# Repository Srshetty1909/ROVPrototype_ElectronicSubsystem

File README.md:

# ROVPrototype_ElectronicSubsystem
The Electronics Architecture for an ROV Prototype meant to test various subsystems for a future AUV before final integration.

Control Architecture:

Power Distribution:

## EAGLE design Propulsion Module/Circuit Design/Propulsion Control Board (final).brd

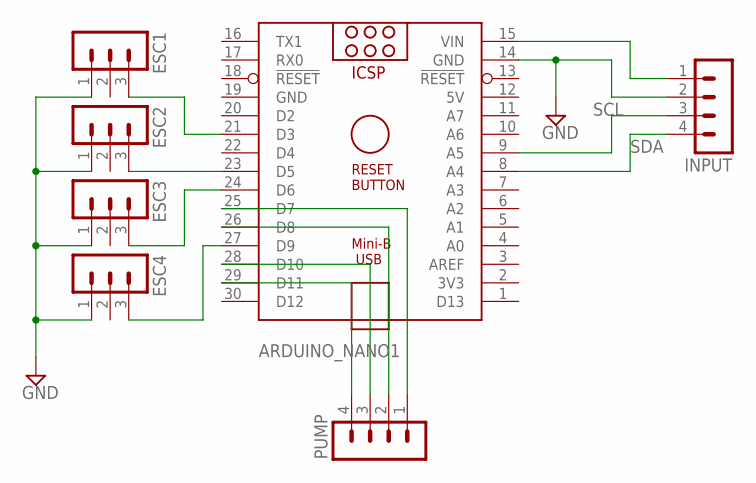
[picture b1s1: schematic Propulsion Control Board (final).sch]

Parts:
ARDUINO_NANO1: ARDUINO_NANO
ESC1, ESC2, ESC3, ESC4: MA03-1
INPUT: MA04-1
PUMP: MA04-1

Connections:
5V: ARDUINO_NANO1.12 (5V)
GND: ARDUINO_NANO1.14 (GND), ARDUINO_NANO1.19 (GND), ESC1.1, ESC2.1, ESC3.1, ESC4.1, INPUT.2
unnamed: ARDUINO_NANO1.21 (D3), ESC1.3
unnamed: ARDUINO_NANO1.23 (D5), ESC2.3
unnamed: ARDUINO_NANO1.24 (D6), ESC3.3
unnamed: ARDUINO_NANO1.27 (D9), ESC4.3
unnamed: ARDUINO_NANO1.25 (D7), PUMP.1
unnamed: ARDUINO_NANO1.26 (D8), PUMP.2
unnamed: ARDUINO_NANO1.28 (D10), PUMP.3
unnamed: ARDUINO_NANO1.29 (D11), PUMP.4
unnamed: ARDUINO_NANO1.15 (VIN), INPUT.1
SCL: ARDUINO_NANO1.9 (A5), INPUT.3
SDA: ARDUINO_NANO1.8 (A4), INPUT.4

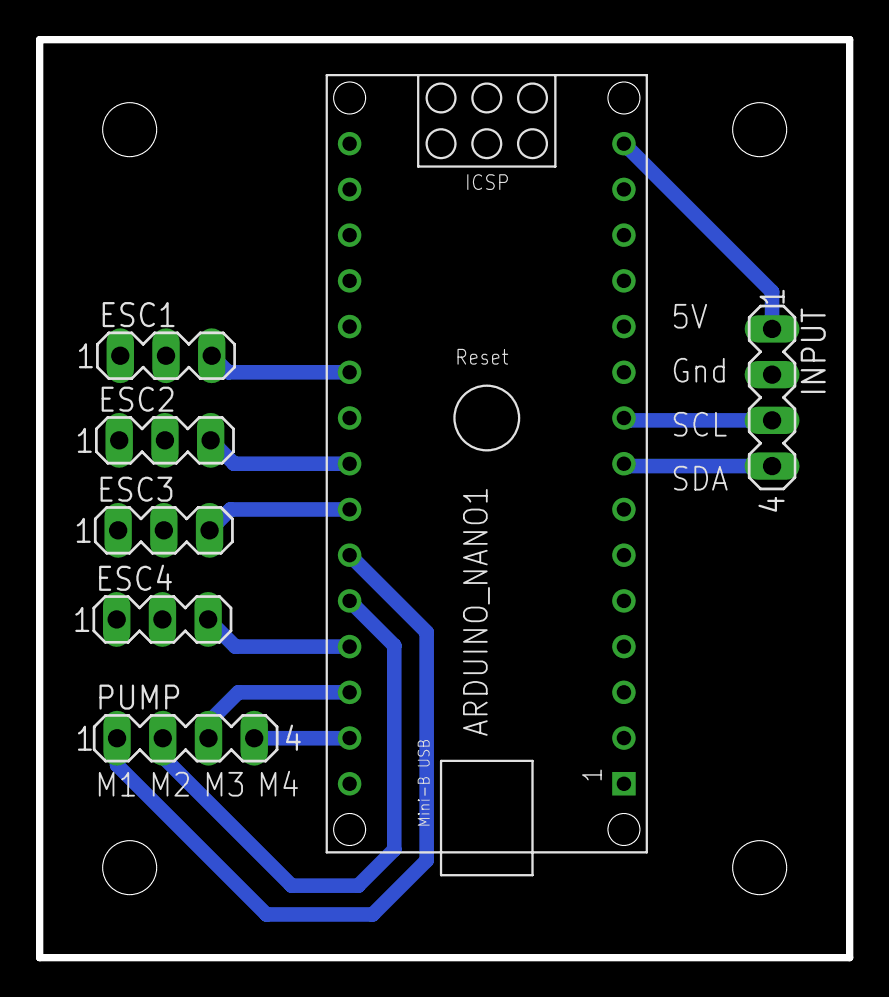
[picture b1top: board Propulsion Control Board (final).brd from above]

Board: 2 copper layers, 45.0 x 51.0 mm, 7 parts (0 on the bottom side), 12 nets.

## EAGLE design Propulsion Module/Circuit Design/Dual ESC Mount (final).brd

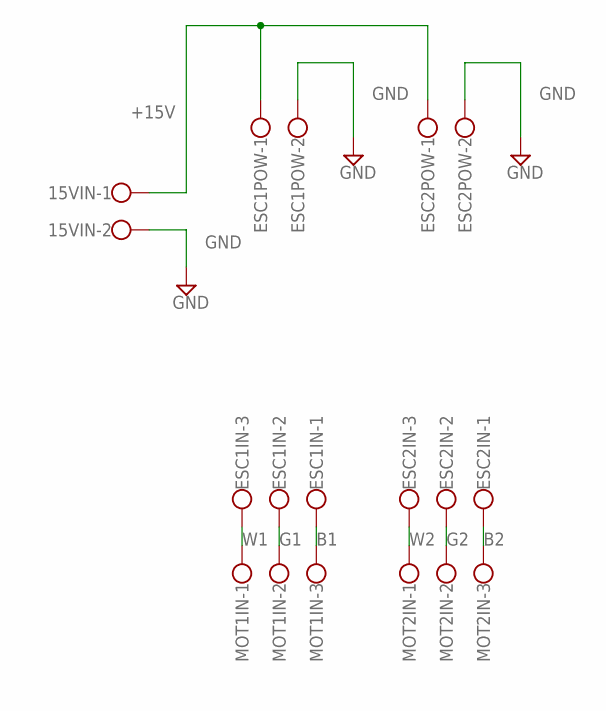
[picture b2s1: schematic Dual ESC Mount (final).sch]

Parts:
15VIN: W237-102
ESC1IN, ESC2IN: W237-103
ESC1POW, ESC2POW: W237-102
MOT1IN, MOT2IN: W237-103

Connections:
+15V: 15VIN.1, ESC1POW.1, ESC2POW.1
B1: ESC1IN.1, MOT1IN.3
B2: ESC2IN.1, MOT2IN.3
G1: ESC1IN.2, MOT1IN.2
G2: ESC2IN.2, MOT2IN.2
GND: 15VIN.2, ESC1POW.2, ESC2POW.2
W1: ESC1IN.3, MOT1IN.1
W2: ESC2IN.3, MOT2IN.1

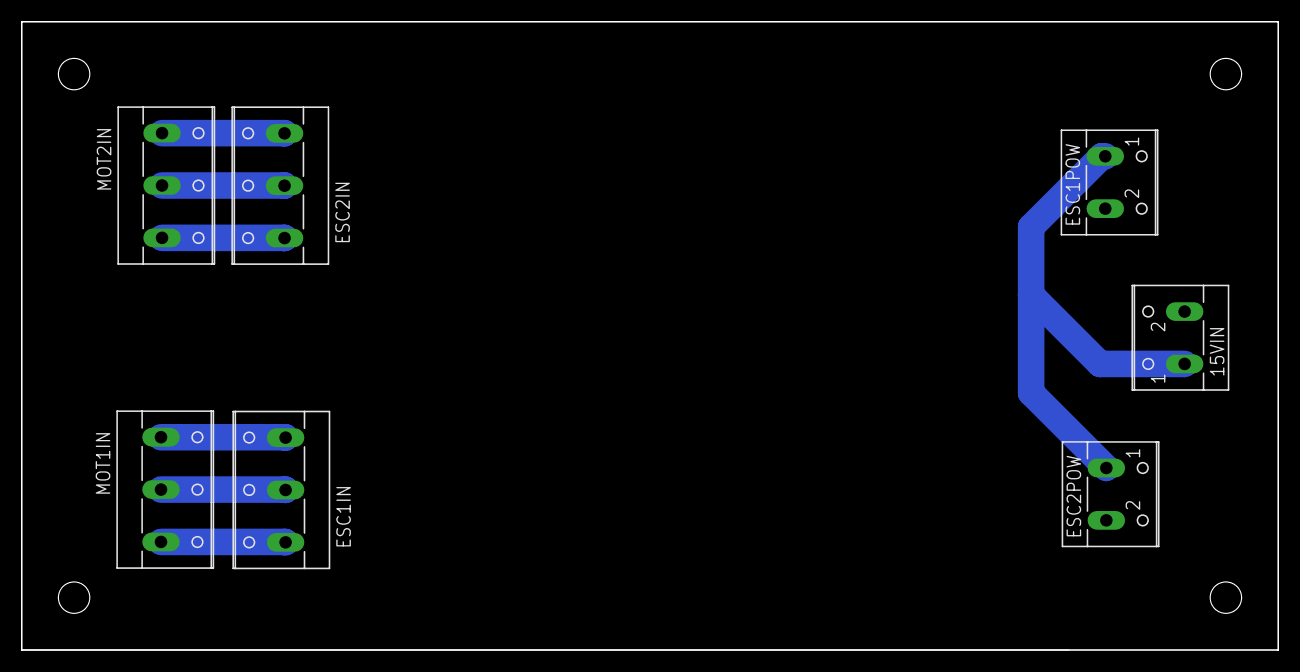
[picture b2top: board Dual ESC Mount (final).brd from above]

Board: 2 copper layers, 120.0 x 60.0 mm, 7 parts (0 on the bottom side), 8 nets.

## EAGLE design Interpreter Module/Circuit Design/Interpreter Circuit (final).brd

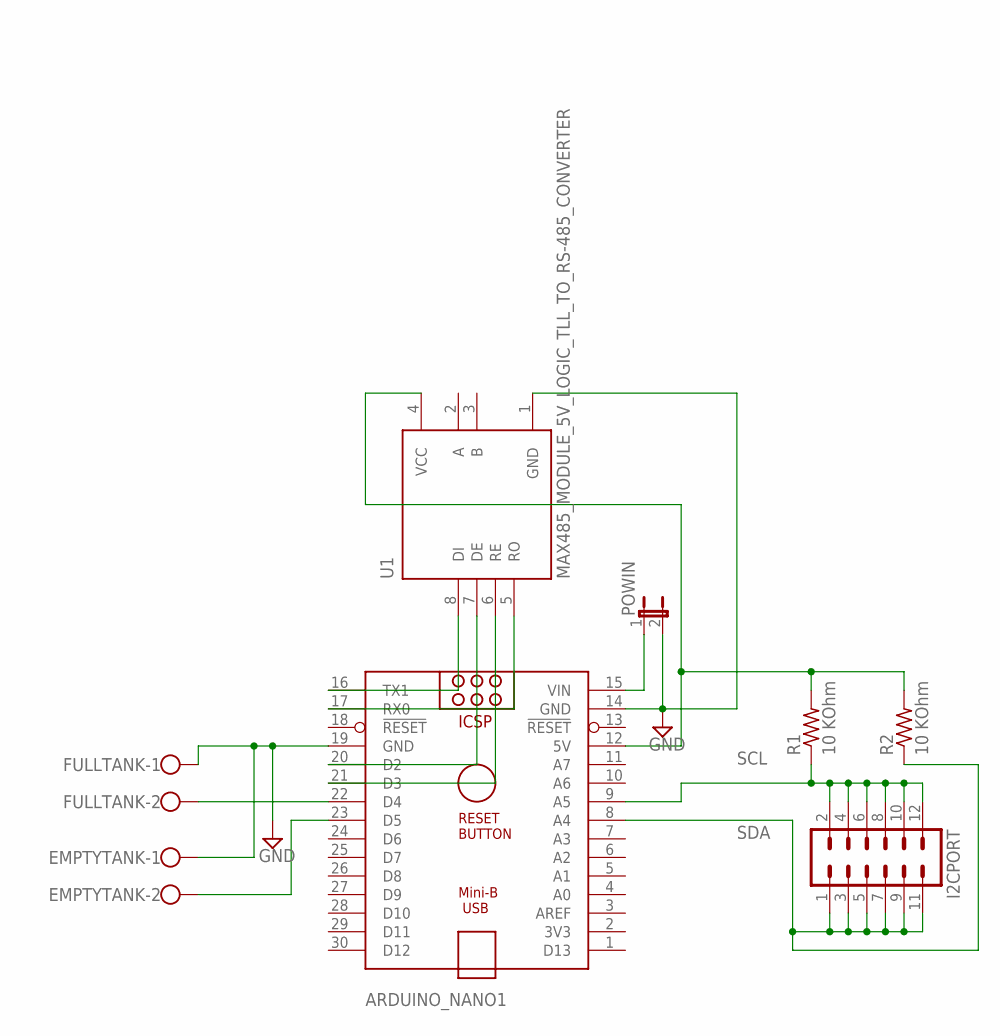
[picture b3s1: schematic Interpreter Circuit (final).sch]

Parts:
ARDUINO_NANO1: ARDUINO_NANO
EMPTYTANK: W237-102
FULLTANK: W237-102
I2CPORT: MA06-2
POWIN: JP1E; JP1
R1, R2: 10 KOhm; 0204/7
U1: MAX485_MODULE_5V_LOGIC_TLL_TO_RS-485_CONVERTER; MODULE_MAX485_MODULE_5V_LOGIC_TLL_TO_RS-485_CONVERTER

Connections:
GND: ARDUINO_NANO1.14 (GND), ARDUINO_NANO1.19 (GND), EMPTYTANK.1, FULLTANK.1, POWIN.2, U1.1 (GND)
unnamed: ARDUINO_NANO1.17 (RX0), U1.5 (RO)
unnamed: ARDUINO_NANO1.16 (TX1), U1.8 (DI)
unnamed: ARDUINO_NANO1.20 (D2), U1.7 (DE)
unnamed: ARDUINO_NANO1.21 (D3), U1.6 (RE)
unnamed: ARDUINO_NANO1.22 (D4), FULLTANK.2
unnamed: ARDUINO_NANO1.12 (5V), R1.2, R2.2, U1.4 (VCC)
unnamed: ARDUINO_NANO1.23 (D5), EMPTYTANK.2
unnamed: ARDUINO_NANO1.15 (VIN), POWIN.1
SCL: ARDUINO_NANO1.9 (A5), I2CPORT.2, I2CPORT.4, I2CPORT.6, I2CPORT.8, I2CPORT.10, I2CPORT.12, R1.1
SDA: ARDUINO_NANO1.8 (A4), I2CPORT.1, I2CPORT.3, I2CPORT.5, I2CPORT.7, I2CPORT.9, I2CPORT.11, R2.1

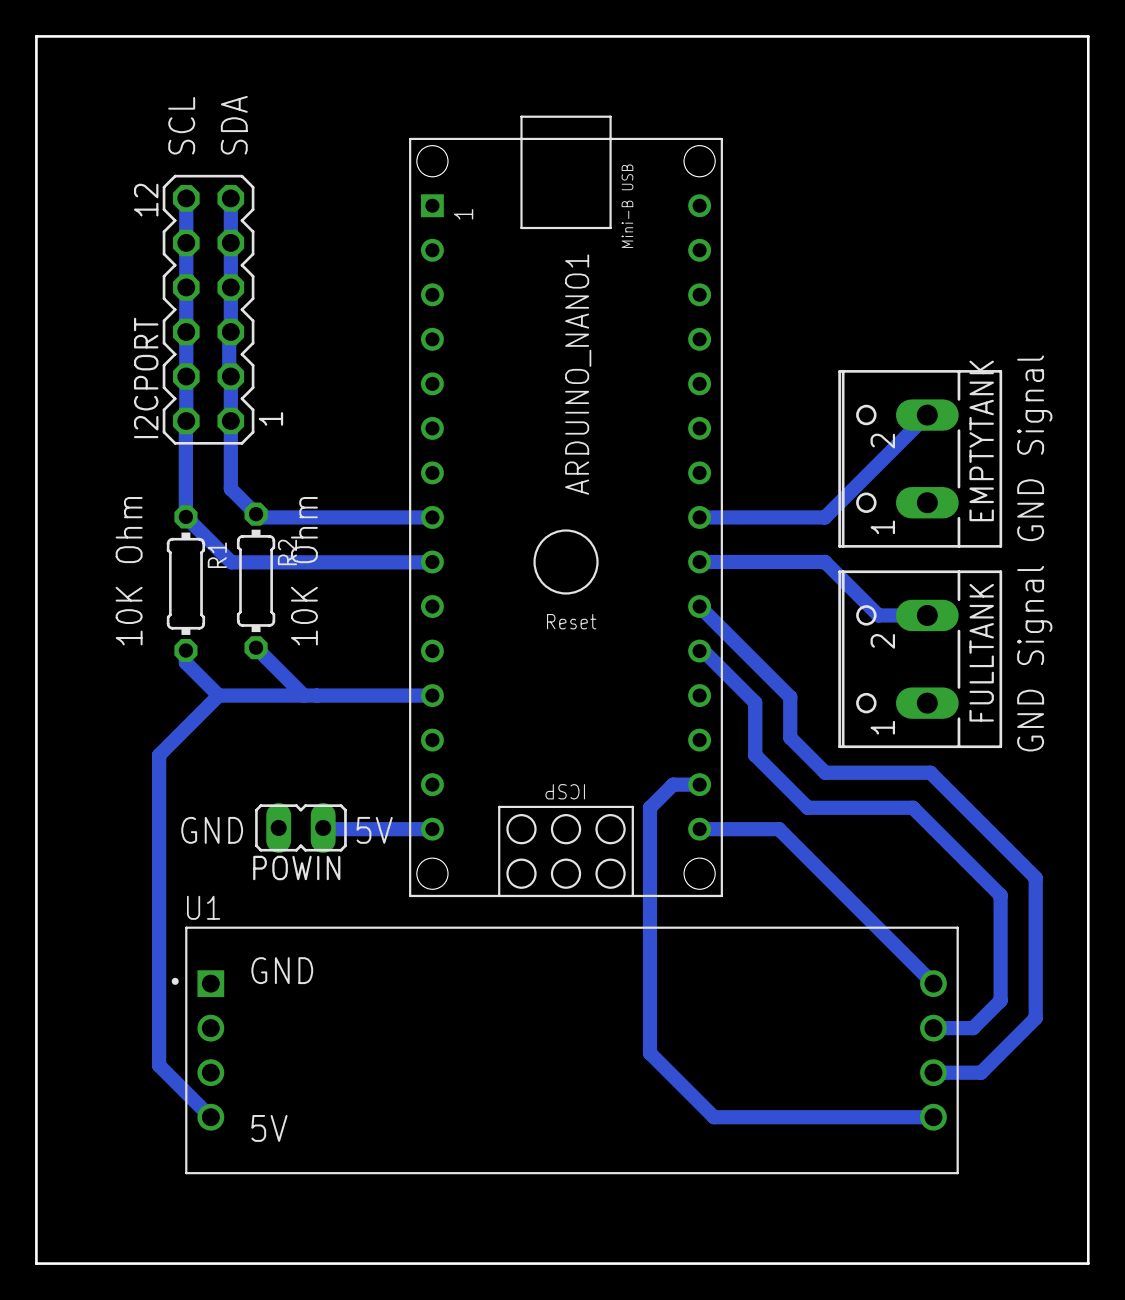
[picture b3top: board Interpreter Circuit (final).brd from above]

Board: 2 copper layers, 60.0 x 70.0 mm, 8 parts (0 on the bottom side), 11 nets.

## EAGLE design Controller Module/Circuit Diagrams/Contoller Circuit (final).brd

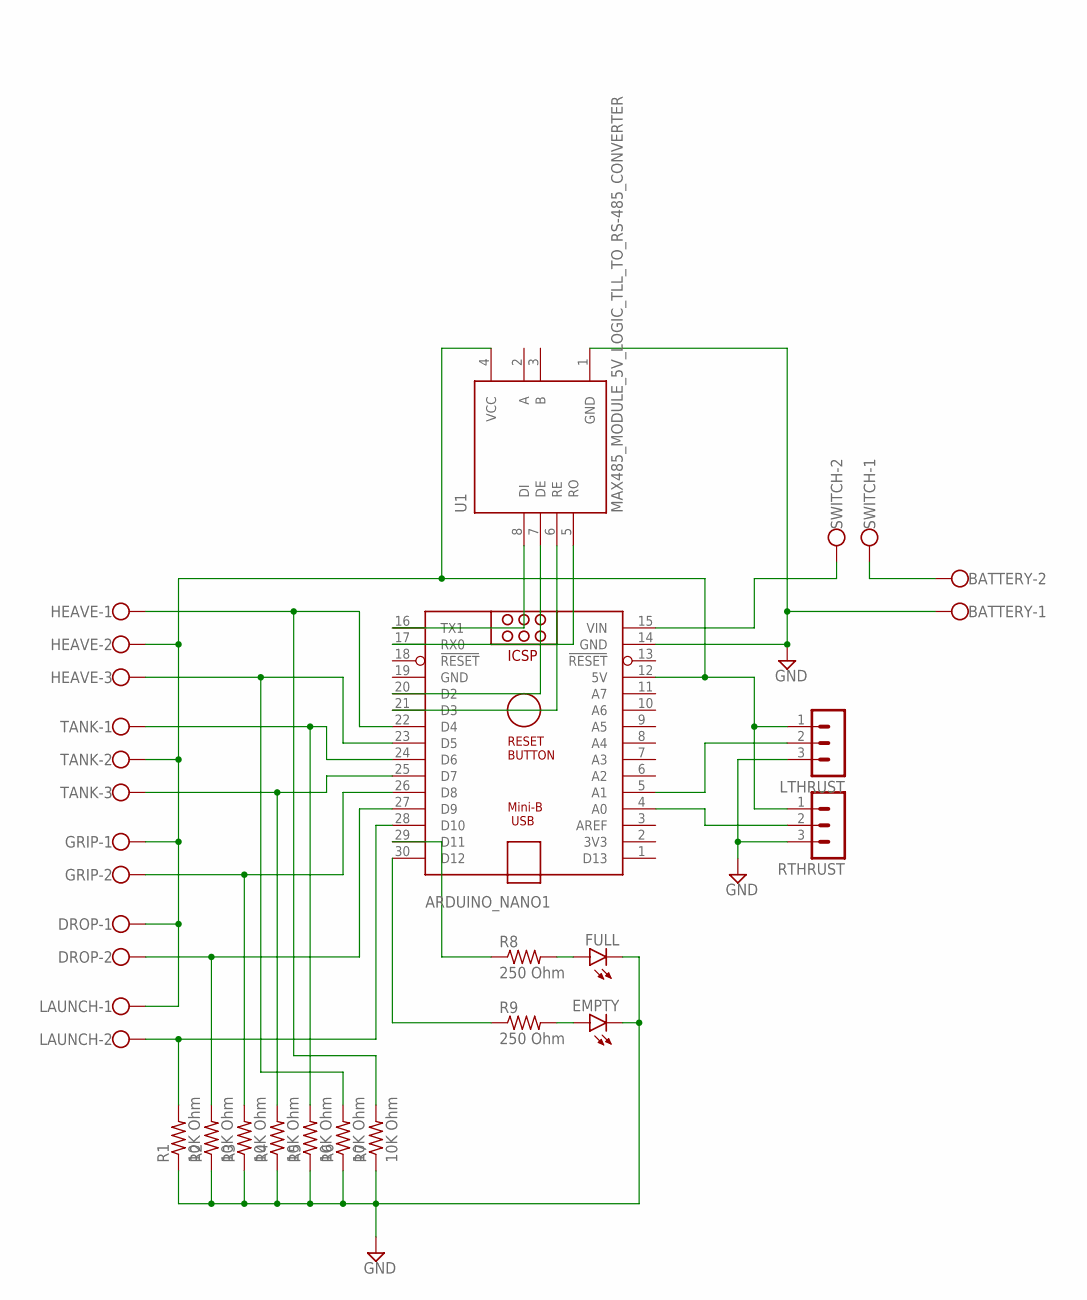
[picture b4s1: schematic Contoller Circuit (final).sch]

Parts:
ARDUINO_NANO1: ARDUINO_NANO
BATTERY: W237-102
DROP: W237-102
EMPTY: LED3MM
FULL: LED3MM
GRIP: W237-102
HEAVE: W237-103
LAUNCH: W237-102
LTHRUST: MA03-1
R1, R2, R3, R4, R5, R6, R7: 10K Ohm; 0204/7
R8, R9: 250 Ohm; 0204/7
RTHRUST: MA03-1
SWITCH: W237-102
TANK: W237-103
U1: MAX485_MODULE_5V_LOGIC_TLL_TO_RS-485_CONVERTER; MODULE_MAX485_MODULE_5V_LOGIC_TLL_TO_RS-485_CONVERTER

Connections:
GND: ARDUINO_NANO1.14 (GND), ARDUINO_NANO1.19 (GND), BATTERY.1, EMPTY.K (C), FULL.K (C), LTHRUST.3, R1.1, R2.1, R3.1, R4.1, R5.1, R6.1, R7.1, RTHRUST.3, U1.1 (GND)
unnamed: ARDUINO_NANO1.12 (5V), DROP.1, GRIP.1, HEAVE.2, LAUNCH.1, LTHRUST.1, RTHRUST.1, TANK.2, U1.4 (VCC)
unnamed: ARDUINO_NANO1.4 (A0), RTHRUST.2
unnamed: ARDUINO_NANO1.20 (D2), U1.7 (DE)
unnamed: ARDUINO_NANO1.21 (D3), U1.6 (RE)
unnamed: FULL.A, R8.2
unnamed: ARDUINO_NANO1.22 (D4), HEAVE.1, R7.2
unnamed: ARDUINO_NANO1.5 (A1), LTHRUST.2
unnamed: ARDUINO_NANO1.15 (VIN), SWITCH.2
unnamed: ARDUINO_NANO1.23 (D5), HEAVE.3, R6.2
unnamed: ARDUINO_NANO1.24 (D6), R5.2, TANK.1
unnamed: ARDUINO_NANO1.25 (D7), R4.2, TANK.3
unnamed: ARDUINO_NANO1.16 (TX1), U1.8 (DI)
unnamed: ARDUINO_NANO1.17 (RX0), U1.5 (RO)
unnamed: ARDUINO_NANO1.26 (D8), GRIP.2, R3.2
unnamed: ARDUINO_NANO1.27 (D9), DROP.2, R2.2
unnamed: ARDUINO_NANO1.28 (D10), LAUNCH.2, R1.2
unnamed: ARDUINO_NANO1.29 (D11), R8.1
unnamed: ARDUINO_NANO1.30 (D12), R9.1
unnamed: EMPTY.A, R9.2
unnamed: BATTERY.2, SWITCH.1

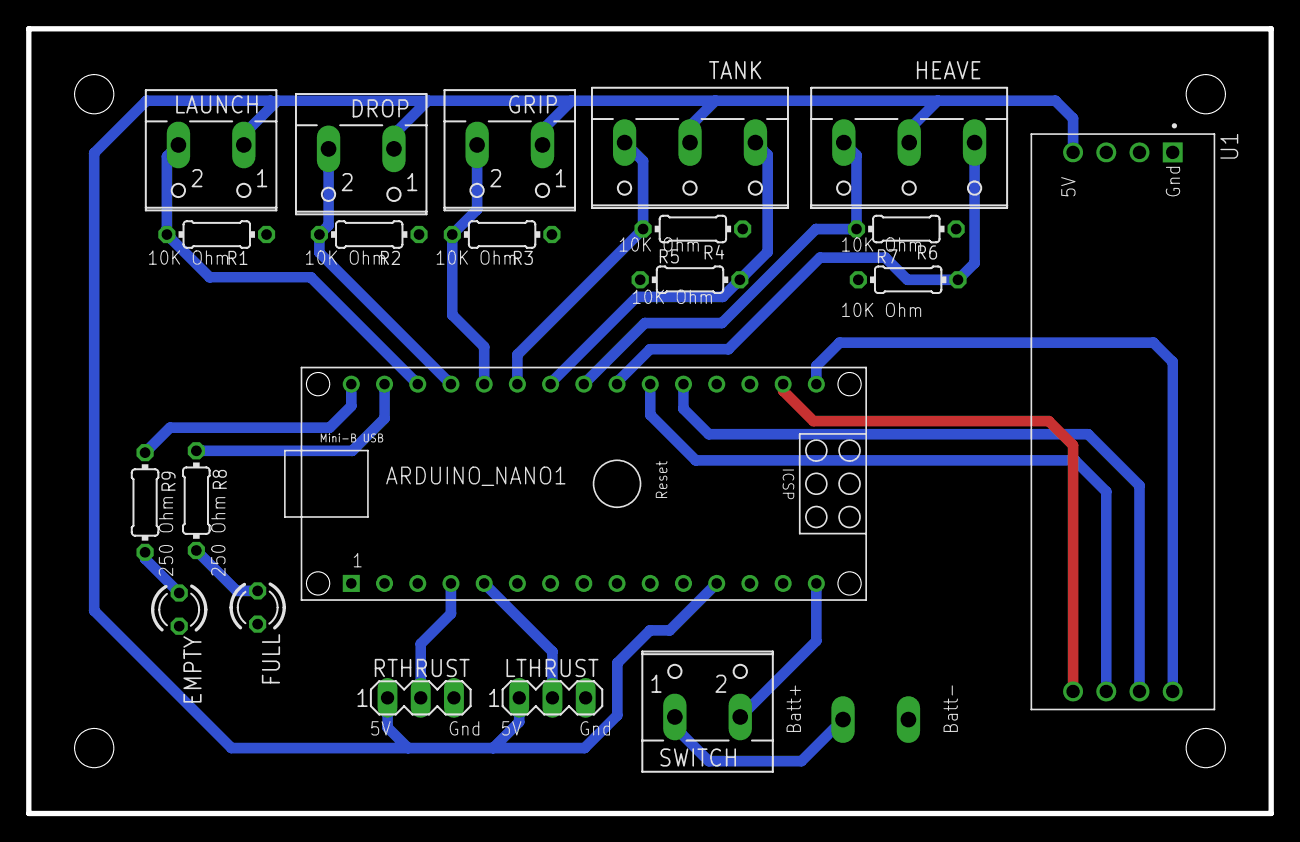
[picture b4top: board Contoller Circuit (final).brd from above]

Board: 2 copper layers, 95.0 x 60.0 mm, 22 parts (1 on the bottom side), 21 nets.

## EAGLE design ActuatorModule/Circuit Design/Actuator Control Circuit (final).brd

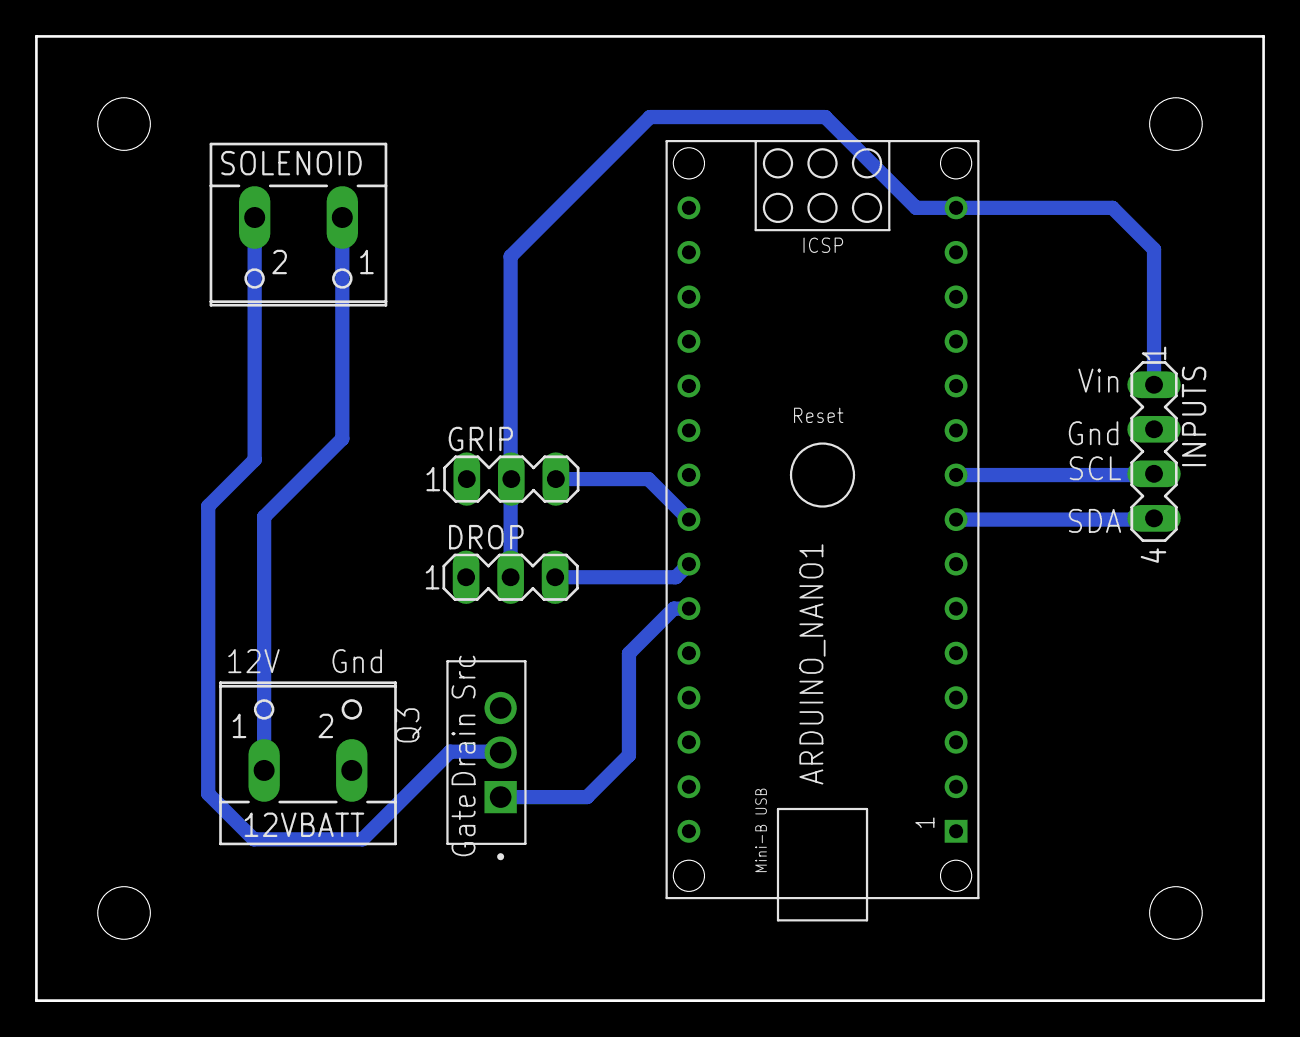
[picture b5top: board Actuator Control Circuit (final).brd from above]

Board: 2 copper layers, 70.0 x 55.0 mm, 7 parts (0 on the bottom side), 9 nets.

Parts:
12VBATT: W237-102
ARDUINO_NANO1: ARDUINO_NANO
DROP: MA03-1
GRIP: MA03-1
INPUTS: MA04-1
Q3: IRF540NPBF; TO254P1054X469X1930-3
SOLENOID: W237-102

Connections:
12VIN: 12VBATT.1, SOLENOID.1
GND: 12VBATT.2, ARDUINO_NANO1.14, ARDUINO_NANO1.19, DROP.1, GRIP.1, INPUTS.2, Q3.3
unnamed: ARDUINO_NANO1.25, Q3.1
unnamed: Q3.2, SOLENOID.2
PWM1: ARDUINO_NANO1.23, GRIP.3
PWM2: ARDUINO_NANO1.24, DROP.3
SCL: ARDUINO_NANO1.9, INPUTS.3
SDA: ARDUINO_NANO1.8, INPUTS.4
VIN: ARDUINO_NANO1.15, DROP.2, GRIP.2, INPUTS.1
